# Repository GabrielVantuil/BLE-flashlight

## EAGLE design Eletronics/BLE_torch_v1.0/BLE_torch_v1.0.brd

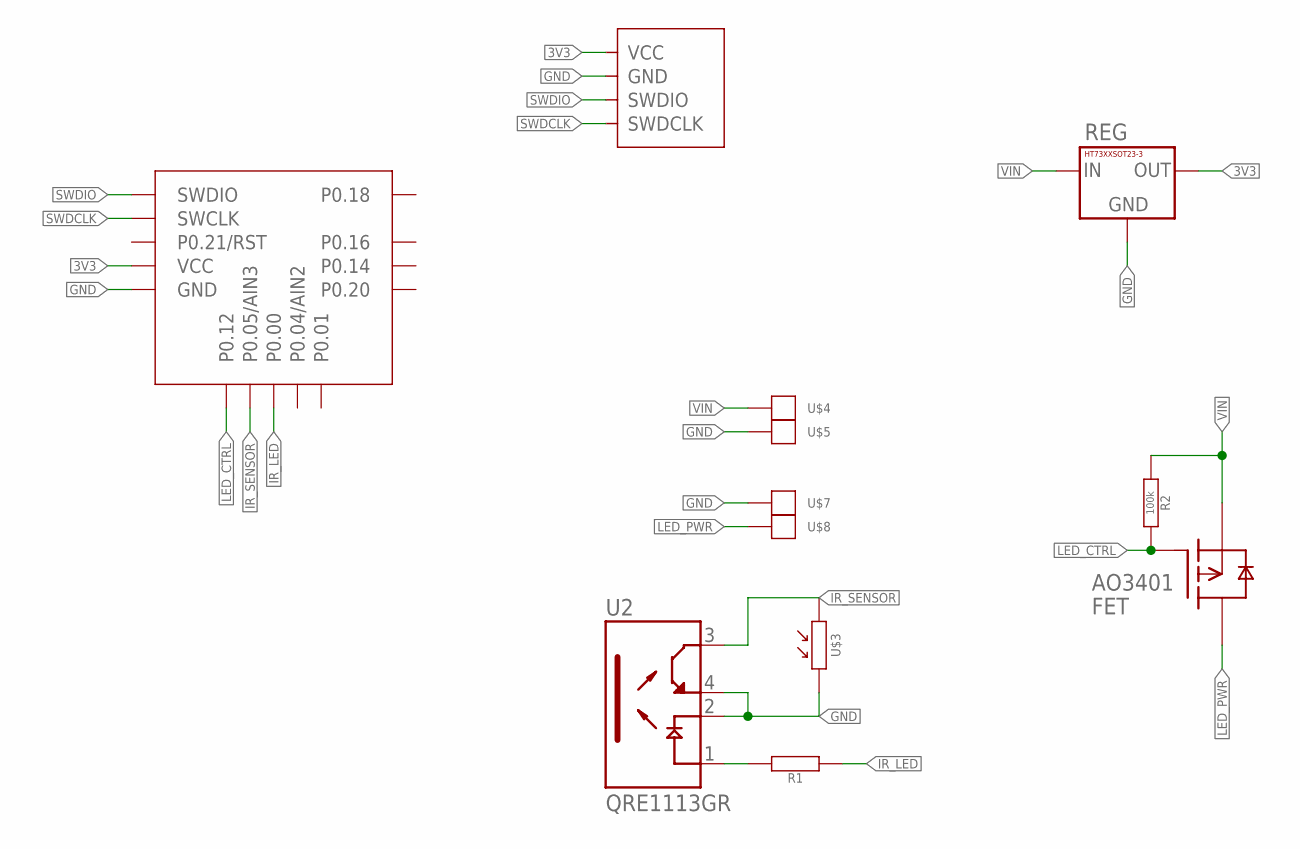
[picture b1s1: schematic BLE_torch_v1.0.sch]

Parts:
FET: AO3401; SOT23-3
R1: RESISTOR0402-RES; 0402-RES
R2: 100k; 0402-RES
REG: HT73XXSOT23-3; SOT23-3
U2: QRE1113GR; SOIC180P460X187-4N
U$2: E104-BT5005A
U$3: LDR_5MM
U$4, U$5: PAD_50X100MIL
U$6: GV_SWD_4P; GV_SWD_1.27MM_4P_SEMI_SMD
U$7, U$8: PAD_1.3X5MM

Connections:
3V3: REG.2 (3.OUT), U$2.VCC, U$6.VCC
GND: REG.1 (2.GND), U2.2 (C), U2.4 (ET), U$2.GND, U$2.GND1 (GND), U$3.P$1, U$5.P$1, U$6.GND, U$7.P$1
IR_LED: R1.1, U$2.P0.00
IR_SENSOR: U2.3 (CT), U$2.P0.05 (P0.05/AIN3), U$3.P$2
LED_CTRL: FET.1 (G), R2.2, U$2.P0.12
LED_PWR: FET.3 (D), U$8.P$1
unnamed: R1.2, U2.1 (A)
SWDCLK: U$2.SWCLK, U$6.SWDCLK
SWDIO: U$2.SWDIO, U$6.SWDIO
VIN: FET.2 (S), R2.1, REG.3 (1.IN), U$4.P$1

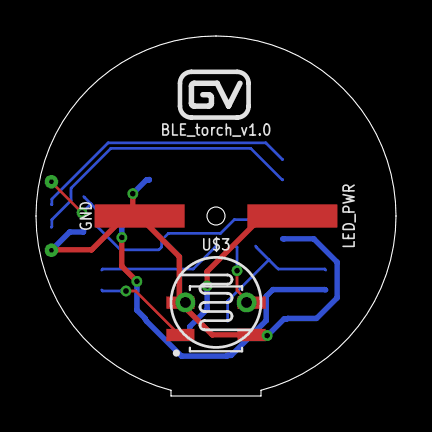
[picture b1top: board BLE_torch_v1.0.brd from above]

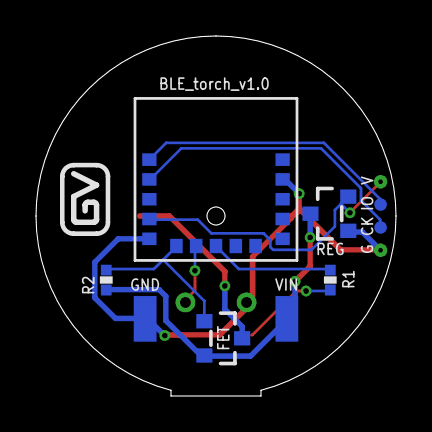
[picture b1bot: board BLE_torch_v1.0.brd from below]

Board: 2 copper layers, 20.0 x 20.0 mm, 14 parts (9 on the bottom side), 10 nets.

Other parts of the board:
U$9, U$10: GV_5MM

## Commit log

2024-05-11 First commit, only basic working, need huge refactor
2024-05-12 Adding gitignore
2024-05-12 Implementing PWM handlers
2024-05-12 Power led at 70% when board is powered
2024-05-12 More precision at setting frequency (~0.001Hz)
2024-05-18 Reorganizing files
2024-05-19 Added eletronics "BLE_torch_v1.0"
2024-05-19 Removing not necessary files
